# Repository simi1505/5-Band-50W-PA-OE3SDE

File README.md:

# 5-Band-50W-PA-OE3SDE
 50W 5-Band (80m, 40m, 30m, 20m and 10m) SSB PA inspired by W6JL.

## Block Diagram

**Figure 1**: Block diagram of 50W 5-Band (80m, 40m, 30m, 20m and 10m) SSB PA.

## Results

**Figure 2**: Setup of 50W PA and LC lowpass filter.

## LC Lowpass Filters

**Figure 3**: Top view of LC lowpass filter PCB.

**Figure 4**: Measurement of LC lowpass filter with NanoVNA.

## **50W Power Amplifier**

**Figure 5**: Top view of 50W PA PCB.

**Figure 6**: Bottom view of 50W PA PCB.

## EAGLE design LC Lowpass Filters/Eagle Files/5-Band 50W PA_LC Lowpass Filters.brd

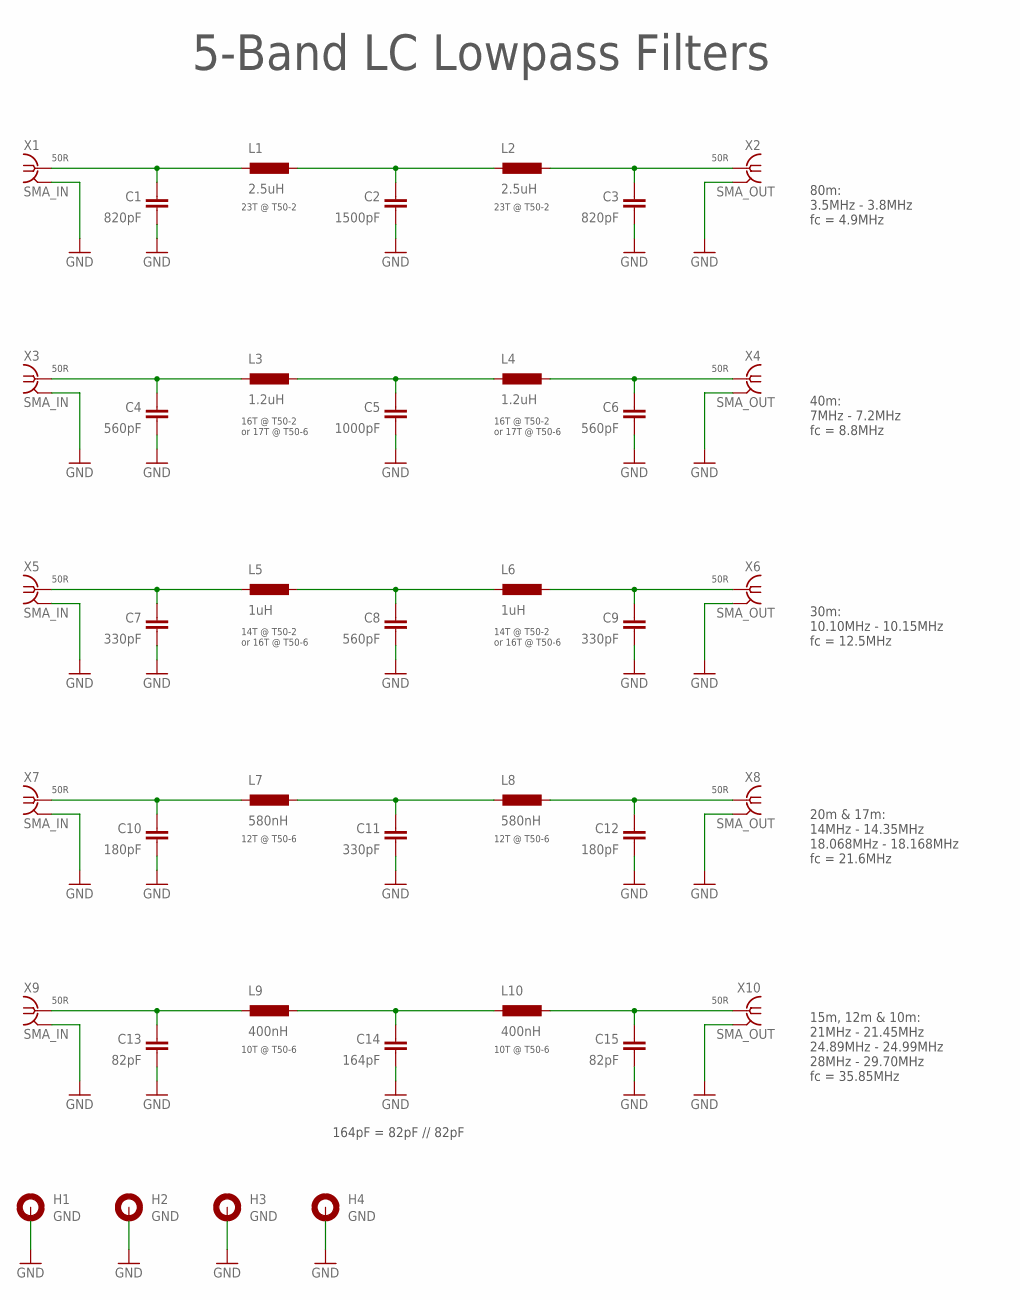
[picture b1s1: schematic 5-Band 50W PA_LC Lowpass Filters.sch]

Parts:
C1, C3: 820pF; C1206K
C2: 1500pF; C1206K
C4, C6, C8: 560pF; C1206K
C5: 1000pF; C1206K
C7, C9, C11: 330pF; C1206K
C10, C12: 180pF; C1206K
C13, C15: 82pF; C1206K
C14: 164pF; C1206K
H1, H2, H3, H4: GND; 3,0-PAD
L1, L2: 2.5uH; T50-6SMD
L3, L4: 1.2uH; T50-6SMD
L5, L6: 1uH; T50-6SMD
L7, L8: 580nH; T50-6SMD
L9, L10: 400nH; T50-6SMD
X1, X3, X5, X7, X9: SMA_IN; J502-ND-142-0711-821/826
X2, X4, X6, X8, X10: SMA_OUT; J502-ND-142-0711-821/826

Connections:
GND: C1.1, C2.1, C3.1, C4.1, C5.1, C6.1, C7.1, C8.1, C9.1, C10.1, C11.1, C12.1, C13.1, C14.1, C15.1, H1.B3,0, H2.B3,0, H3.B3,0, H4.B3,0, X1.G@1 (2), X1.G@2 (2), X1.G@3 (2), X1.G@4 (2), X2.G@1 (2), X2.G@2 (2), X2.G@3 (2), X2.G@4 (2), X3.G@1 (2), X3.G@2 (2), X3.G@3 (2), X3.G@4 (2), X4.G@1 (2), X4.G@2 (2), X4.G@3 (2), X4.G@4 (2), X5.G@1 (2), X5.G@2 (2), X5.G@3 (2), X5.G@4 (2), X6.G@1 (2), X6.G@2 (2), X6.G@3 (2), X6.G@4 (2), X7.G@1 (2), X7.G@2 (2), X7.G@3 (2), X7.G@4 (2), X8.G@1 (2), X8.G@2 (2), X8.G@3 (2), X8.G@4 (2), X9.G@1 (2), X9.G@2 (2), X9.G@3 (2), X9.G@4 (2), X10.G@1 (2), X10.G@2 (2), X10.G@3 (2), X10.G@4 (2)
unnamed: C2.2, L1.P$2 (2), L2.P$1 (1)
unnamed: C4.2, L3.P$1 (1), X3.1
unnamed: C3.2, L2.P$2 (2), X2.1
unnamed: C1.2, L1.P$1 (1), X1.1
unnamed: C6.2, L4.P$2 (2), X4.1
unnamed: C5.2, L3.P$2 (2), L4.P$1 (1)
unnamed: C7.2, L5.P$1 (1), X5.1
unnamed: C9.2, L6.P$2 (2), X6.1
unnamed: C8.2, L5.P$2 (2), L6.P$1 (1)
unnamed: C10.2, L7.P$1 (1), X7.1
unnamed: C12.2, L8.P$2 (2), X8.1
unnamed: C11.2, L7.P$2 (2), L8.P$1 (1)
unnamed: C13.2, L9.P$1 (1), X9.1
unnamed: C15.2, L10.P$2 (2), X10.1
unnamed: C14.2, L9.P$2 (2), L10.P$1 (1)

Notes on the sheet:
50R
80m: 3.5MHz - 3.8MHz fc = 4.9MHz
23T @ T50-2
5-Band LC Lowpass Filters
40m: 7MHz - 7.2MHz fc = 8.8MHz
16T @ T50-2 or 17T @ T50-6
30m: 10.10MHz - 10.15MHz fc = 12.5MHz
14T @ T50-2 or 16T @ T50-6
20m & 17m: 14MHz - 14.35MHz 18.068MHz - 18.168MHz fc = 21.6MHz
12T @ T50-6
15m, 12m & 10m: 21MHz - 21.45MHz 24.89MHz - 24.99MHz 28MHz - 29.70MHz fc = 35.85MHz
10T @ T50-6
164pF = 82pF // 82pF

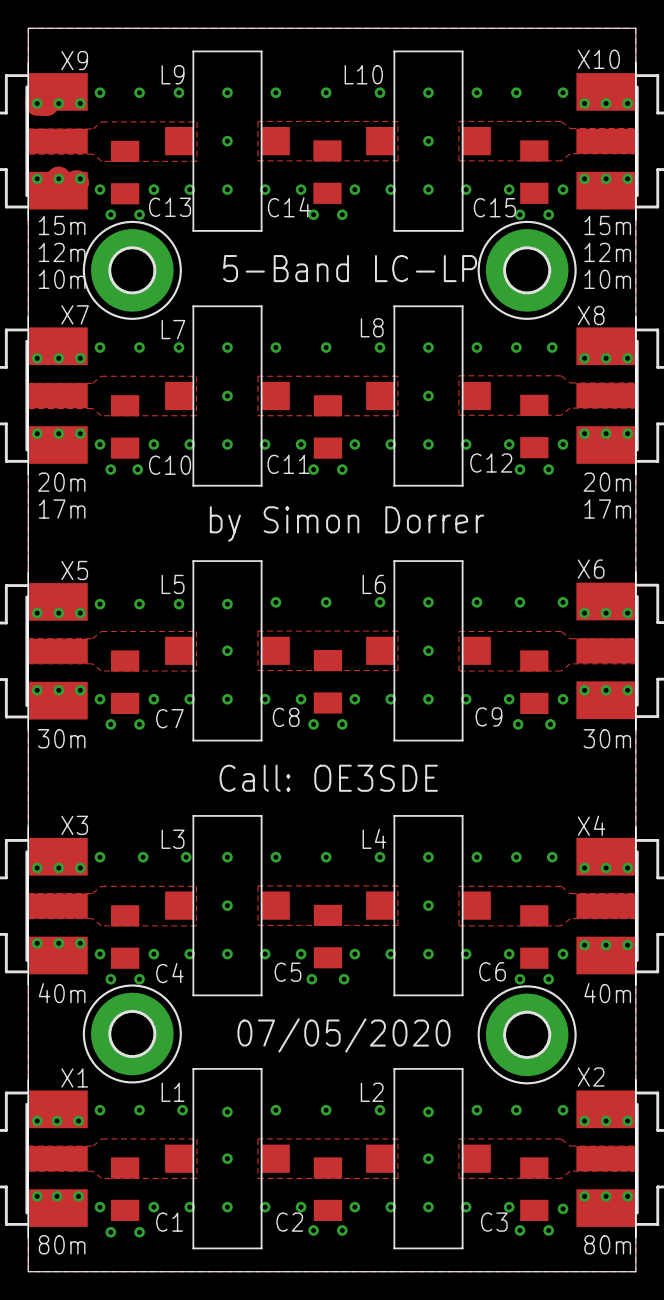
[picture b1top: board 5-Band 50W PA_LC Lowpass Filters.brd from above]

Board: 2 copper layers, 43.0 x 88.0 mm, 39 parts (0 on the bottom side), 16 nets.

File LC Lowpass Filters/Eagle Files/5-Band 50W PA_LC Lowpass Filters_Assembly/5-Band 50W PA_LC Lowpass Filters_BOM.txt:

Partlist exported from E:/Simon Dorrer/DIY Projekte/Amateurfunkprojekte/DIY KITs/5-Band 50W PA/LC Lowpass Filters/Eagle Files/5-Band 50W PA_LC Lowpass Filters.sch at 19/05/2020 19:35

Qty Value   Device               Package                  Parts               Description                                           MF                 MPN          OC_FARNELL OC_NEWARK POPULARITY SPICEPREFIX
2   1.2uH   T50-6                T50-6SMD                 L3, L4                                                                                                                                               
1   1000pF  C-EUC1206K           C1206K                   C5                  CAPACITOR, European symbol                                                                                 13         C          
1   1500pF  C-EUC1206K           C1206K                   C2                  CAPACITOR, European symbol                                                                                 13         C          
1   164pF   C-EUC1206K           C1206K                   C14                 CAPACITOR, European symbol                                                                                 13         C          
2   180pF   C-EUC1206K           C1206K                   C10, C12            CAPACITOR, European symbol                                                                                 13         C          
2   1uH     T50-6                T50-6SMD                 L5, L6                                                                                                                                               
2   2.5uH   T50-6                T50-6SMD                 L1, L2                                                                                                                                               
3   330pF   C-EUC1206K           C1206K                   C7, C9, C11         CAPACITOR, European symbol                                                                                 13         C          
2   400nH   T50-6                T50-6SMD                 L9, L10                                                                                                                                              
3   560pF   C-EUC1206K           C1206K                   C4, C6, C8          CAPACITOR, European symbol                                                                                 13         C          
2   580nH   T50-6                T50-6SMD                 L7, L8                                                                                                                                               
2   820pF   C-EUC1206K           C1206K                   C1, C3              CAPACITOR, European symbol                                                                                 13         C          
2   82pF    C-EUC1206K           C1206K                   C13, C15            CAPACITOR, European symbol                                                                                 13         C          
4   GND     MOUNT-PAD-ROUND3.0   3,0-PAD                  H1, H2, H3, H4      MOUNTING PAD, round                                                                                                              
5   SMA_IN  SMA-142-0711-821/826 J502-ND-142-0711-821/826 X1, X3, X5, X7, X9  SMA 50 Ohm End Launch Jack Receptacle - Round Contact JOHNSON COMPONENTS 142-0711-821 1019328    16F3627                         
5   SMA_OUT SMA-142-0711-821/826 J502-ND-142-0711-821/826 X2, X4, X6, X8, X10 SMA 50 Ohm End Launch Jack Receptacle - Round Contact JOHNSON COMPONENTS 142-0711-821 1019328    16F3627

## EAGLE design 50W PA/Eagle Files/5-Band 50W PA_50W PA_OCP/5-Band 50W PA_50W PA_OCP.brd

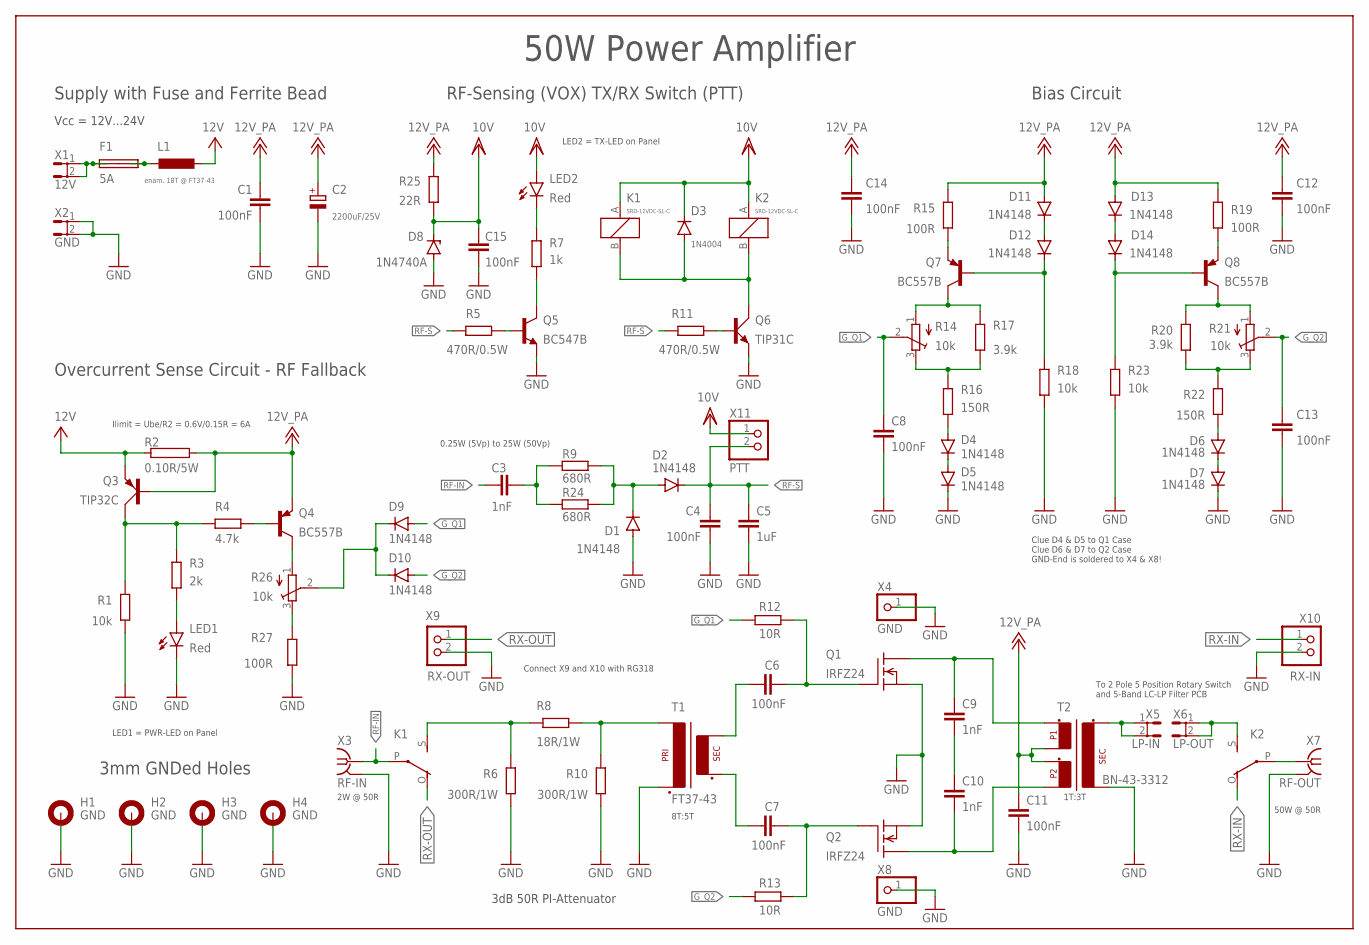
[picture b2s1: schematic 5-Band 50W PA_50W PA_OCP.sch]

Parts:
C1, C4, C6, C7, C8, C11, C12, C13, C14, C15: 100nF; C0805
C2: 2200uF/25V; E7,5-16
C3: 1nF; C0805
C5: 1uF; C0805
C9, C10: 1nF; C1206K
D1, D2, D9, D10, D11, D12, D13, D14: 1N4148; SOD323-W
D3: 1N4004; DO41-10
D4, D5, D6, D7: 1N4148; DO35-7
D8: 1N4740A; DO41Z10
F1: 5A; SHK20L
H1, H2, H3, H4: GND; 3,0-PAD
K1, K2: SRD-12VDC-SL-C
L1: enam. 18T @ FT37-43; T50-6SMD
LED1, LED2: Red; LED5MM
Q1, Q2: IRFZ24; TO220
Q3: TIP32C; TO220AV
Q4, Q7, Q8: BC557B; TO92-EBC
Q5: BC547B; TO92-CBE
Q6: TIP31C; TO220AV
R1, R18, R23: 10k; R0805
R2: 0.10R/5W; MNS-5
R3: 2k; R0805
R4: 4.7k; R0805
R5, R11: 470R/0.5W; 0207/10
R6, R10: 300R/1W; 0414/15
R7: 1k; R0805
R8: 18R/1W; 0414/15
R9, R24: 680R; R0805
R12, R13: 10R; 0207/10
R14, R21, R26: 10k; 3223G
R15, R19, R27: 100R; R0805
R16, R22: 150R; R0805
R17, R20: 3.9k; R0805
R25: 22R; 0207/10
T1: FT37-43; FT37-43SMD
T2: BN-43-3312; BN-43-3312CENTERTAPSMD
X1: 12V; ST6,3
X2: GND; ST6,3
X3: RF-IN; J502-ND-142-0711-821/826
X4, X8: GND; 1X01
X5: LP-IN; ST6,3
X6: LP-OUT; ST6,3
X7: RF-OUT; J502-ND-142-0711-821/826
X9: RX-OUT; 1X02
X10: RX-IN; 1X02
X11: PTT; 1X02

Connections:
+12V: C1.2, C2.+, C11.2, C12.2, C14.2, D11.A, D13.A, Q3.B, Q4.E, R2.2, R15.2, R19.2, R25.2, T2.P$2 (P1_2), T2.P$3 (P2_1)
GND: C1.1, C2.-, C4.1, C5.1, C8.1, C11.1, C12.1, C13.1, C14.1, C15.1, D1.A, D5.C, D7.C, D8.A, H1.B3,0, H2.B3,0, H3.B3,0, H4.B3,0, LED1.K (C), Q1.3 (S), Q2.3 (S), Q5.E, Q6.E, R1.1, R6.1, R10.1, R18.1, R23.1, R27.1, T1.P$2 (P2), T2.S$2 (S2), X2.1, X2.2, X3.G@1 (GND), X3.G@2 (GND), X3.G@3 (GND), X3.G@4 (GND), X4.1, X7.G@1 (GND), X7.G@2 (GND), X7.G@3 (GND), X7.G@4 (GND), X8.1, X9.2, X10.2
G_Q1: C8.2, D9.A, R12.2, R14.2 (S)
G_Q2: C13.2, D10.A, R13.2, R21.2 (S)
unnamed: C6.2, T1.S$1 (S1)
unnamed: C7.2, T1.S$2 (S2)
unnamed: LED2.K (C), R7.1
unnamed: Q8.C, R20.2, R21.1 (A)
unnamed: Q7.E, R15.1
unnamed: C9.1, Q1.2 (D), T2.P$1 (P1_1)
unnamed: R20.1, R21.3 (E), R22.2
unnamed: C10.2, Q2.2 (D), T2.P$4 (P2_2)
unnamed: K1.S, R6.2, R8.2
unnamed: K2.P, X7.1 (RF)
unnamed: R8.1, R10.2, T1.P$1 (P1)
unnamed: D9.C, D10.C, R26.2 (S)
unnamed: D6.C, D7.A
unnamed: Q8.E, R19.1
unnamed: Q7.C, R14.1 (A), R17.2
unnamed: D4.C, D5.A
unnamed: R14.3 (E), R16.2, R17.1
unnamed: D4.A, R16.1
unnamed: D6.A, R22.1
unnamed: D12.C, Q7.B, R18.2
unnamed: C6.1, Q1.1 (G), R12.1
unnamed: C7.1, Q2.1 (G), R13.1
unnamed: K2.S, X6.1, X6.2
unnamed: D3.A, K1.B, K2.B, Q6.C
unnamed: D1.C, D2.A, R9.1, R24.1
unnamed: D14.C, Q8.B, R23.2
unnamed: Q6.B, R11.1
unnamed: F1.1A, F1.1B, X1.1, X1.2
unnamed: R26.3 (E), R27.2
unnamed: F1.2A, F1.2B, L1.P$1 (1)
unnamed: D11.C, D12.A
unnamed: Q5.C, R7.2
unnamed: Q5.B, R5.1
unnamed: C3.1, R9.2, R24.2
unnamed: Q3.C, R1.2, R3.2, R4.2
unnamed: C9.2, C10.1
unnamed: LED1.A, R3.1
unnamed: Q4.B, R4.1
unnamed: T2.S$1 (S1), X5.1, X5.2
unnamed: D13.C, D14.A
unnamed: Q4.C, R26.1 (A)
RF-IN: C3.2, K1.P, X3.1 (RF)
RF-S: C4.2, C5.2, D2.C, R5.2, R11.2, X11.2
RX-IN: K2.O, X10.1
RX-OUT: K1.O, X9.1
VCC: L1.P$2 (2), Q3.E, R2.1
VDD: C15.2, D3.C, D8.C, K1.A, K2.A, LED2.A, R25.1, X11.1

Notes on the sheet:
2W @ 50R
50W @ 50R
Clue D4 & D5 to Q1 Case Clue D6 & D7 to Q2 Case GND-End is soldered to X4 & X8!
1T:3T
8T:5T
50W Power Amplifier
Bias Circuit
Supply with Fuse and Ferrite Bead
3mm GNDed Holes
Overcurrent Sense Circuit - RF Fallback
RF-Sensing (VOX) TX/RX Switch (PTT)
3dB 50R PI-Attenuator
Vcc = 12V...24V
Ilimit = Ube/R2 = 0.6V/0.15R = 6A
To 2 Pole 5 Position Rotary Switch and 5-Band LC-LP Filter PCB
LED1 = PWR-LED on Panel
0.25W (5Vp) to 25W (50Vp)
LED2 = TX-LED on Panel
Connect X9 and X10 with RG318

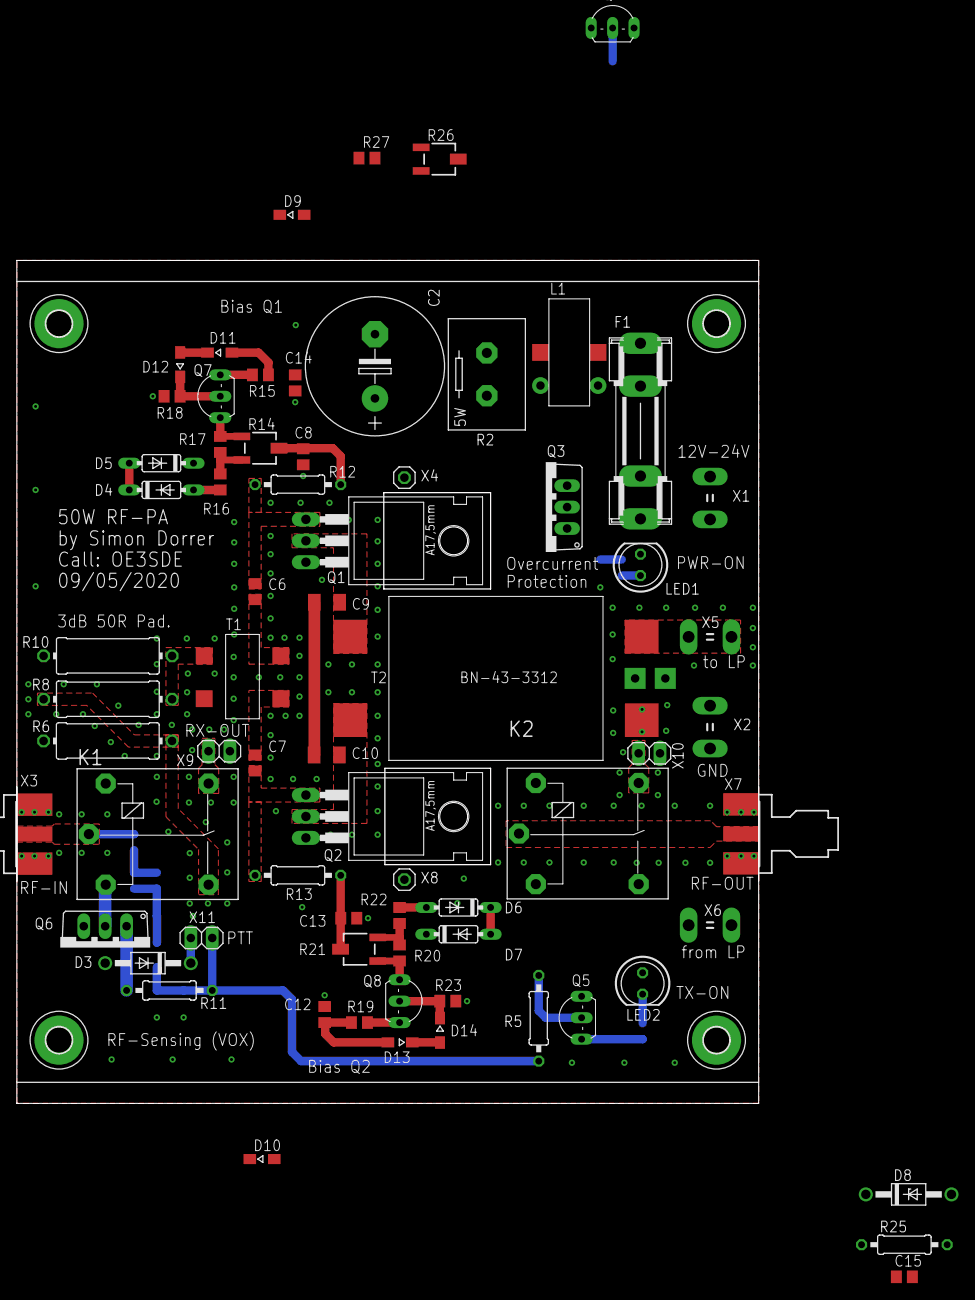
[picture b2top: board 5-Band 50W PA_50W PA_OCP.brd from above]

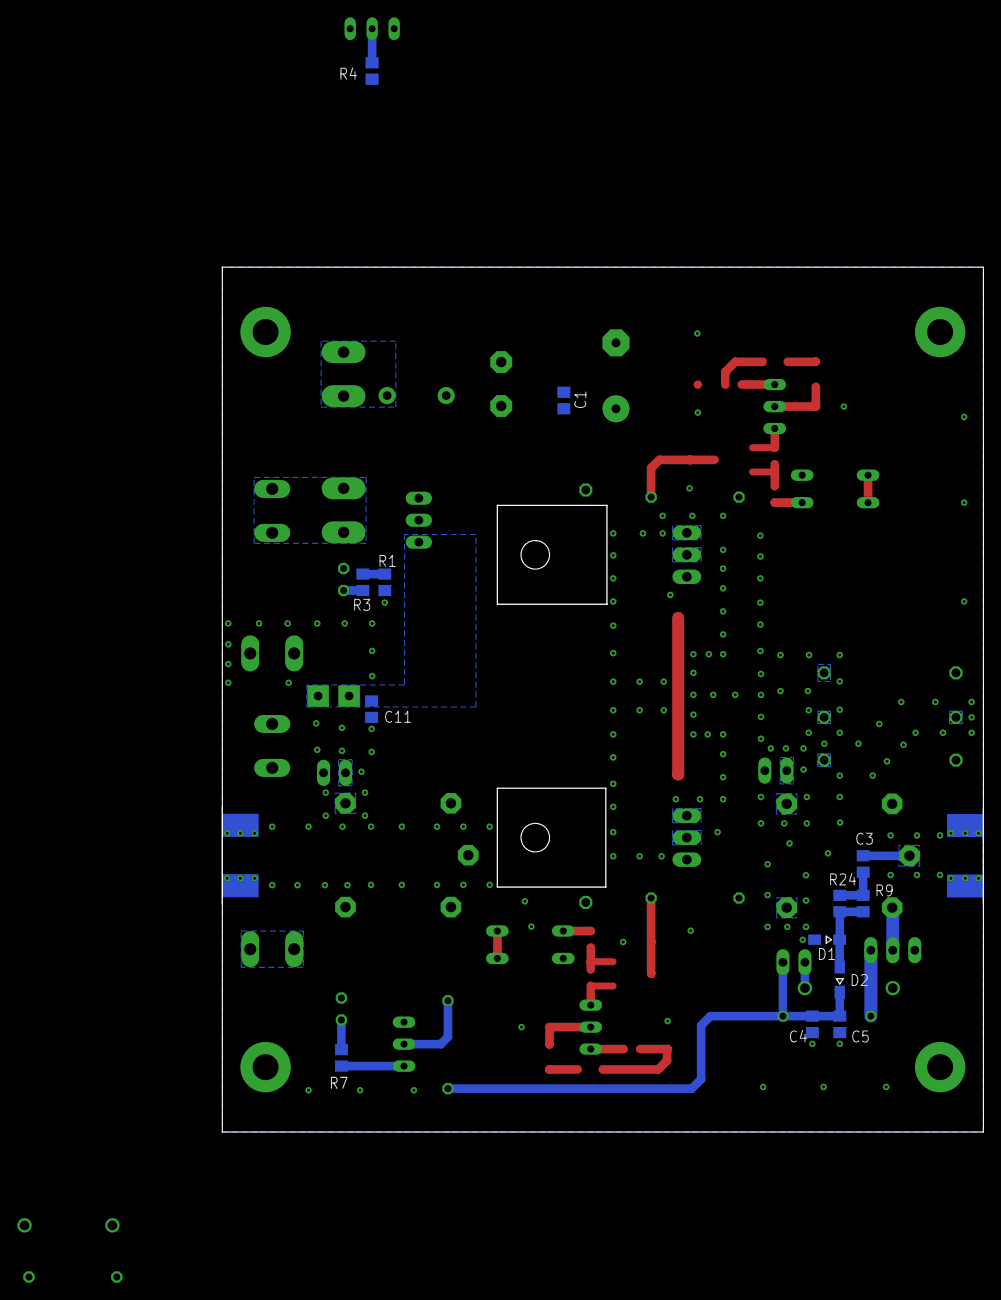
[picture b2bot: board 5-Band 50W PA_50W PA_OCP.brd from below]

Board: 2 copper layers, 88.0 x 100.0 mm, 87 parts (13 on the bottom side), 51 nets.
